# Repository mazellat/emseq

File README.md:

# EMSEQ
EMSEQ is a Eurorack 12hp matrix sequencer, providing two sequences of up to 16 steps each. The length and input clock division/multiplication can also be tweaked thanks to the integrated interface.

## The project
It began in March 2020, but has seen many improvements since, hence this repository. The design files will be available as KiCAD files, and the firmware code will be written in C, meant for the STM32 over the Platformio/Arduino framework. I might as well try out Keil/HAL versions of the firmware.

## Progress
As of mid-April 2021, the project is being ported from EasyEDA to KiCAD, thus the emptiness of this repository in its early stage.
- [x] Create repo
- [x] Parts layout and interface
- [ ] Port the project over KiCAD
- [ ] Reroute and generate Gerber files
- [ ] Define better user experience
- [ ] Upgrade code from older ATMega328p V1.1
- [ ] Create front panel
- [ ] Create user manual/cheat sheet
- [ ] Update module website page

## Features overview
* 12HP 3U Eurorack size
* Two sequences of up to 16 steps
* CV/Gate output pair for each sequence
* Clock input and output
* Reset input, reset button
* 64-LED matrix interface
* Pitch and clock division potentiometers
* Multiple playing modes (forward, backwards, pendulum and random)
* Many more to come!

## Contributing to the project
You can suggest some features/upgrades to the project. If you want more details or have a special need, mail me at thomas@electronicmilkshake.com. I have a lot of other projects to come so stick around!

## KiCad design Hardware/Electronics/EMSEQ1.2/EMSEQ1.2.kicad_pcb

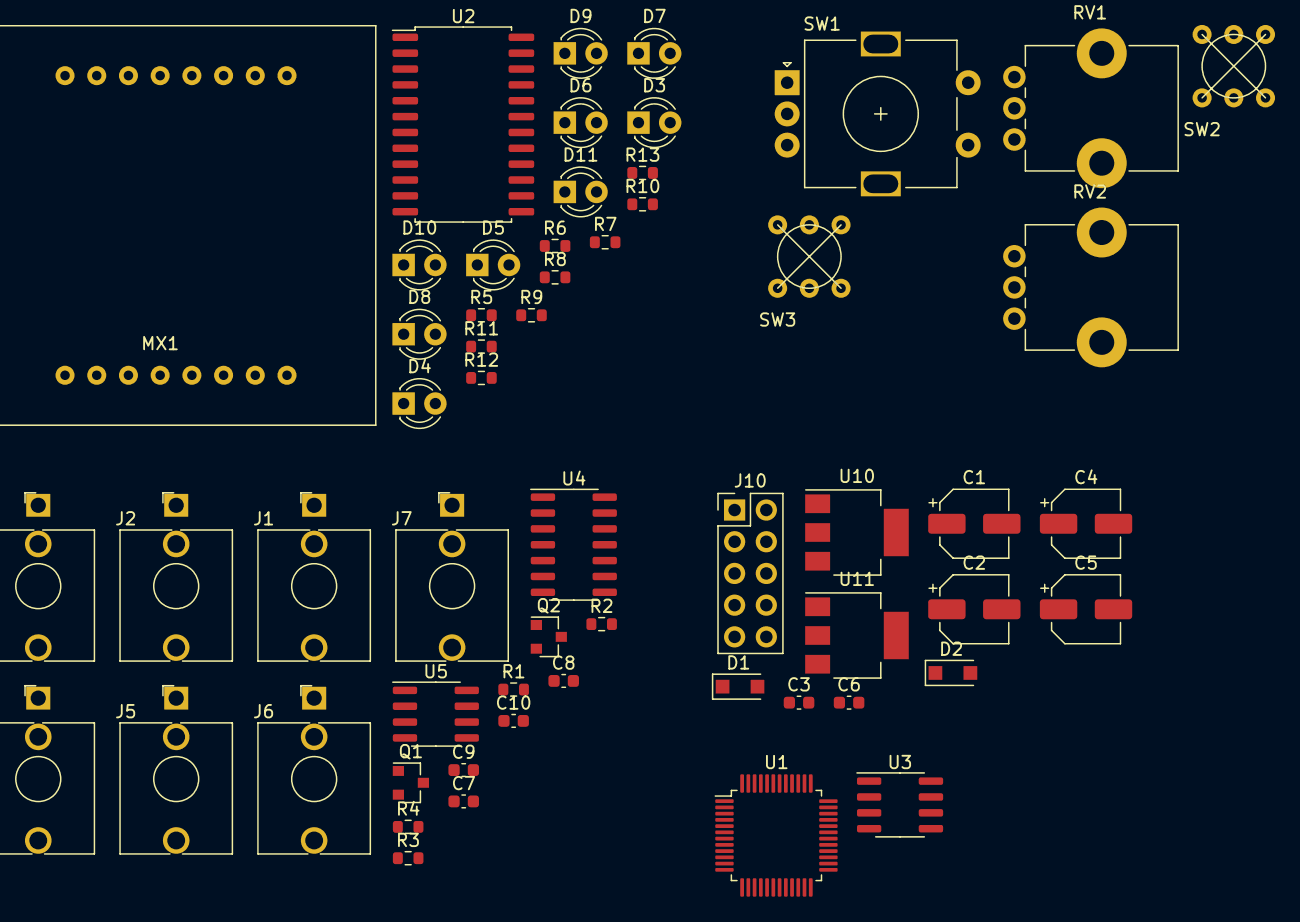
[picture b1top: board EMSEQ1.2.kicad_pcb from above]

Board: 2 copper layers, 57 parts (0 on the bottom side), 26 nets, no tracks yet.

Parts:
C1, C2, C4, C5: 22u; CP_Elec_5x5.3
C3, C6, C7, C8, C9, C10: 100n; C_0603_1608Metric
D1, D2: 1N5819; D_SOD-123F
D3, D4, D5, D6, D7, D8, D9, D10, D11: LED; LED_D3.0mm
J1, J2, J3, J4, J5, J6, J7: AudioJack2_SwitchT; Jack_3.5mm_QingPu_WQP-PJ398SM_Vertical_CircularHoles
J10: Conn_02x05_Counter_Clockwise; PinHeader_2x05_P2.54mm_Vertical
MX1: 1088AS
Q1, Q2: MMBT3904; SOT-23
R1, R2: 100k; R_0603_1608Metric
R3, R4: 10k; R_0603_1608Metric
R5, R6, R7, R8, R9, R10, R11, R12, R13: 1k; R_0603_1608Metric
RV1, RV2: R_POT; Potentiometer_Alps_RK09K_Single_Vertical
SW1: Rotary_Encoder_Switch; RotaryEncoder_Alps_EC11E-Switch_Vertical_H20mm
SW2, SW3: PB6148-L
U1: STM32F103C8Tx; LQFP-48_7x7mm_P0.5mm
U2: MAX7219; SOIC-24W_7.5x15.4mm_P1.27mm
U3: MCP4822; SOIC-8_3.9x4.9mm_P1.27mm
U4: TL074; SOIC-14_3.9x8.7mm_P1.27mm
U5: TL072; SOIC-8_3.9x4.9mm_P1.27mm
U10: LM1117-5.0; SOT-223-3_TabPin2
U11: LM1117-3.3; SOT-223-3_TabPin2

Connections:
+3V3: C5.1, R3.1, R4.1, U1.1, U1.9, U1.24, U1.36, U1.48, U11.2
+5V: C2.1, C4.1, U10.2, U11.3
+12V: C1.1, C7.1, C8.1, D1.1, J10.1, J10.10, U4.4, U5.8, U10.3
-12V: C9.1, C10.1, D2.2, J10.5, J10.6, U4.11, U5.4
GND: C1.2, C2.2, C3.2, C4.2, C5.2, C6.2, C7.2, C8.2, C9.2, C10.2, D1.2, D2.1, D3.1, D4.1, D5.1, D6.1, D7.1, D8.1, D9.1, D10.1, D11.1, J1.S, J2.S, J3.S, J4.S, J5.S, J6.S, J7.S, J10.2, J10.3, J10.4, J10.7, J10.8, J10.9, Q1.2, Q2.2, U1.8, U1.23, U1.35, U1.47, U10.1, U11.1
unnamed: D3.2, R5.1
unnamed: D4.2, R6.1
unnamed: D5.2, R7.1
unnamed: D6.2, R8.1
unnamed: D7.2, R9.1
unnamed: D8.2, R10.1
unnamed: D9.2, R11.1
unnamed: D10.2, R12.1
unnamed: D11.2, R13.1
unnamed: J1.T, R1.2
unnamed: J2.T, R2.2
unnamed: J3.T, U5.6, U5.7
unnamed: J4.T, U4.1, U4.2
unnamed: J5.T, U4.6, U4.7
unnamed: J6.T, U4.8, U4.9
unnamed: J7.T, U4.13, U4.14
unnamed: Q1.1, R1.1
unnamed: Q1.3, R3.2
unnamed: Q2.1, R2.1
unnamed: Q2.3, R4.2
unnamed: U2.4, U2.9

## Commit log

2021-04-13 Update README.md
    Initial REAMDE and project definition
2021-04-13 Update README.md
    Extended to-do list and added features
2021-09-02 Initial schematic commit
2021-09-03 Adding software project
